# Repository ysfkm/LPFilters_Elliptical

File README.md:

# LPFilters Elliptical

## Summary
- Set of 10 discrete PCBs, each a 5th-order passive Elliptic Low Pass Filter (LC ladder), covering cutoff frequencies from 1kHz to 1MHz.
- Each board ships with front/back panels and an aluminum enclosure; designed via markimicrowave (LC synthesis), LTSpice (deviation simulation), and KiCad (PCB + panel layout), with Claude assisting on JLCPCB basic-parts substitution and KiCad design duplication.

## Specs
- **Input:** IN (raw signal)
- **Output:** OUT (filtered signal)
- **Description:** Includes 10 separate boards of 5th order Elliptic Low Pass Filters that use passive elements, mainly LC ladders
- **Cutoffs:** 1kHz, 2kHz, 5kHz, 10kHz, 20kHz, 50kHz, 100kHz, 200kHz, 500kHz, 1MHz
- Includes front/back panels with labels and aluminum encasings
- **PCB:** 77mm x 21.5mm / 4 Layer
- **Aluminum box:** K1-2525-H7-L80 (25mm x 25mm x 80mm)
- **Panel size:** 25mm x 25mm

## Design Process / Notes
- Used markimicrowave to come up with LC values and circuit topology
- Used Claude to browse JLCPCB for available basic parts replacing the extended parts
- Used LTSpice for simulation to monitor deviations due to imperfect components & the swap of extended parts into basic parts
- Assembled circuit & PCB in KiCad (utilized Claude to duplicate designs and update footprint/symbols)
- Made front/back panel in KiCad as a PCB

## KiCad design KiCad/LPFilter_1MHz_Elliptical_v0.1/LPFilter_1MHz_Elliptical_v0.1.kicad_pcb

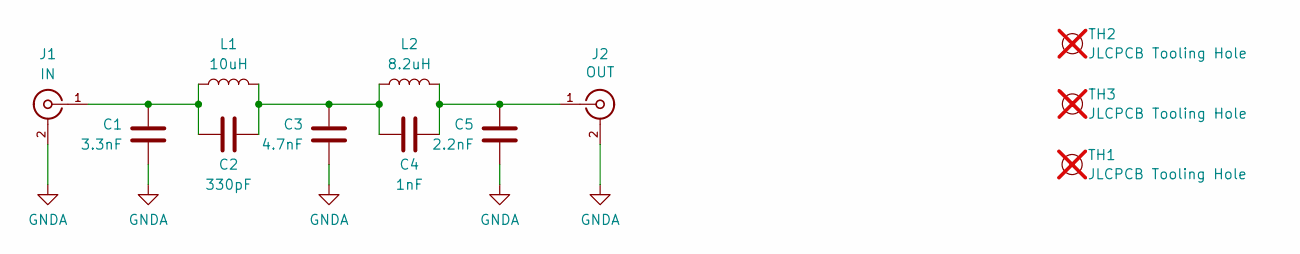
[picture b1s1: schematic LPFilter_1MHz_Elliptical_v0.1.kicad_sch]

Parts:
C1: 3.3nF; C_0603_1608Metric; LCSC C1613
C2: 330pF; C_0603_1608Metric; LCSC C1664
C3: 4.7nF; C_0603_1608Metric; LCSC C53987
C4: 1nF; C_0603_1608Metric; LCSC C1588
C5: 2.2nF; C_0603_1608Metric; LCSC C1604
J1: IN; C2837587-ANT-TH_KH-BNC50-3511; LCSC C2837587
J2: OUT; C2837587-ANT-TH_KH-BNC50-3511; LCSC C2837587
L1: 10uH; C167223-IND-SMD_L7.3-W6.8; LCSC C167223
L2: 8.2uH; C167222-IND-SMD_L7.0-W6.6_FXL0630; LCSC C167222
TH1, TH2, TH3: JLCPCB Tooling Hole; ToolingHoles; not fitted

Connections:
GNDA: C1.2, C3.2, C5.2, J1.2, J1.3, J1.4, J2.2, J2.3, J2.4
unnamed: C2.2, C3.1, C4.1, L1.2, L2.1
unnamed: C1.1, C2.1, J1.1 (OUT), L1.1
unnamed: C4.2, C5.1, J2.1 (OUT), L2.2

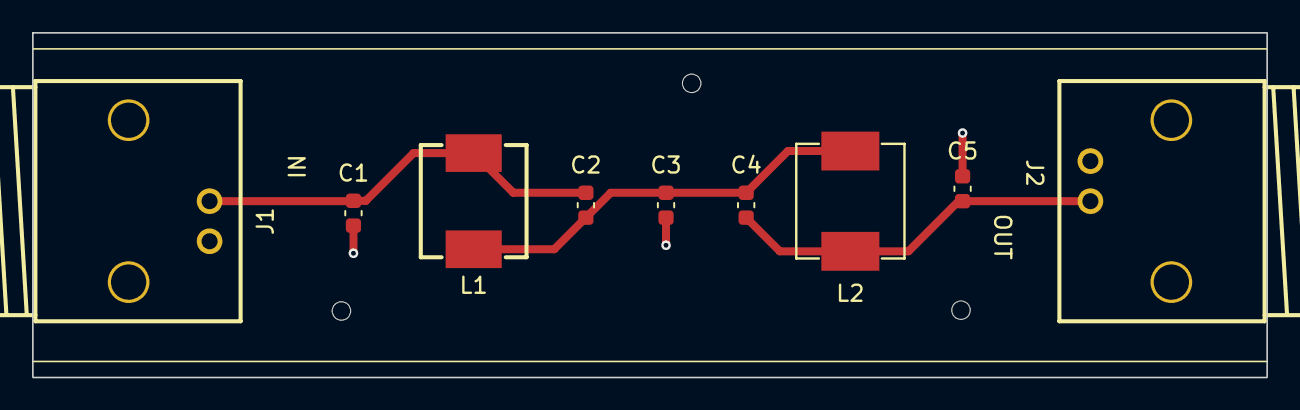
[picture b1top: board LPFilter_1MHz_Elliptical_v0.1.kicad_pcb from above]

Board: 4 copper layers, 77.0 x 21.5 mm, 13 parts (0 on the bottom side), 4 nets.

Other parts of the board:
Aluminum Box: K1-2525-H7-L80
